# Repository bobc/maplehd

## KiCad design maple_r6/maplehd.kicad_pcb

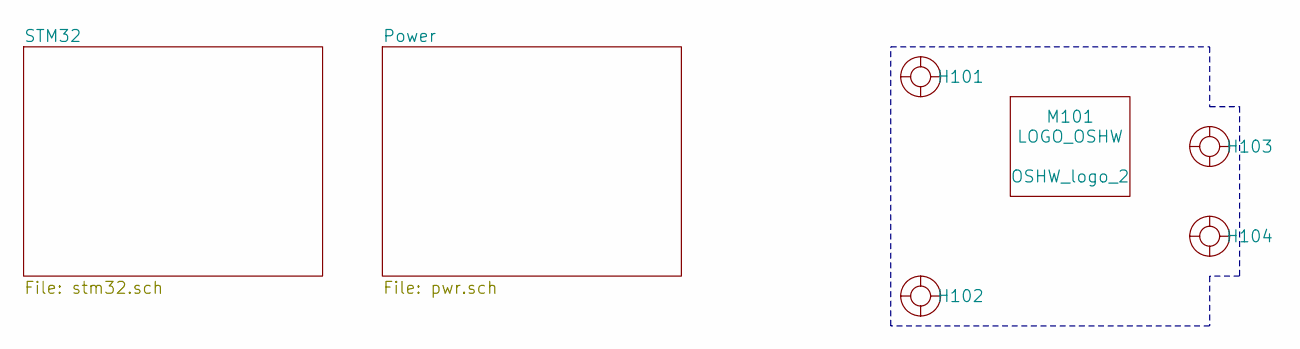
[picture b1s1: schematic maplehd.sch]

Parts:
H101, H102, H103, H104: HOLE_RMC
M101: LOGO_OSHW; OSHW_logo_2

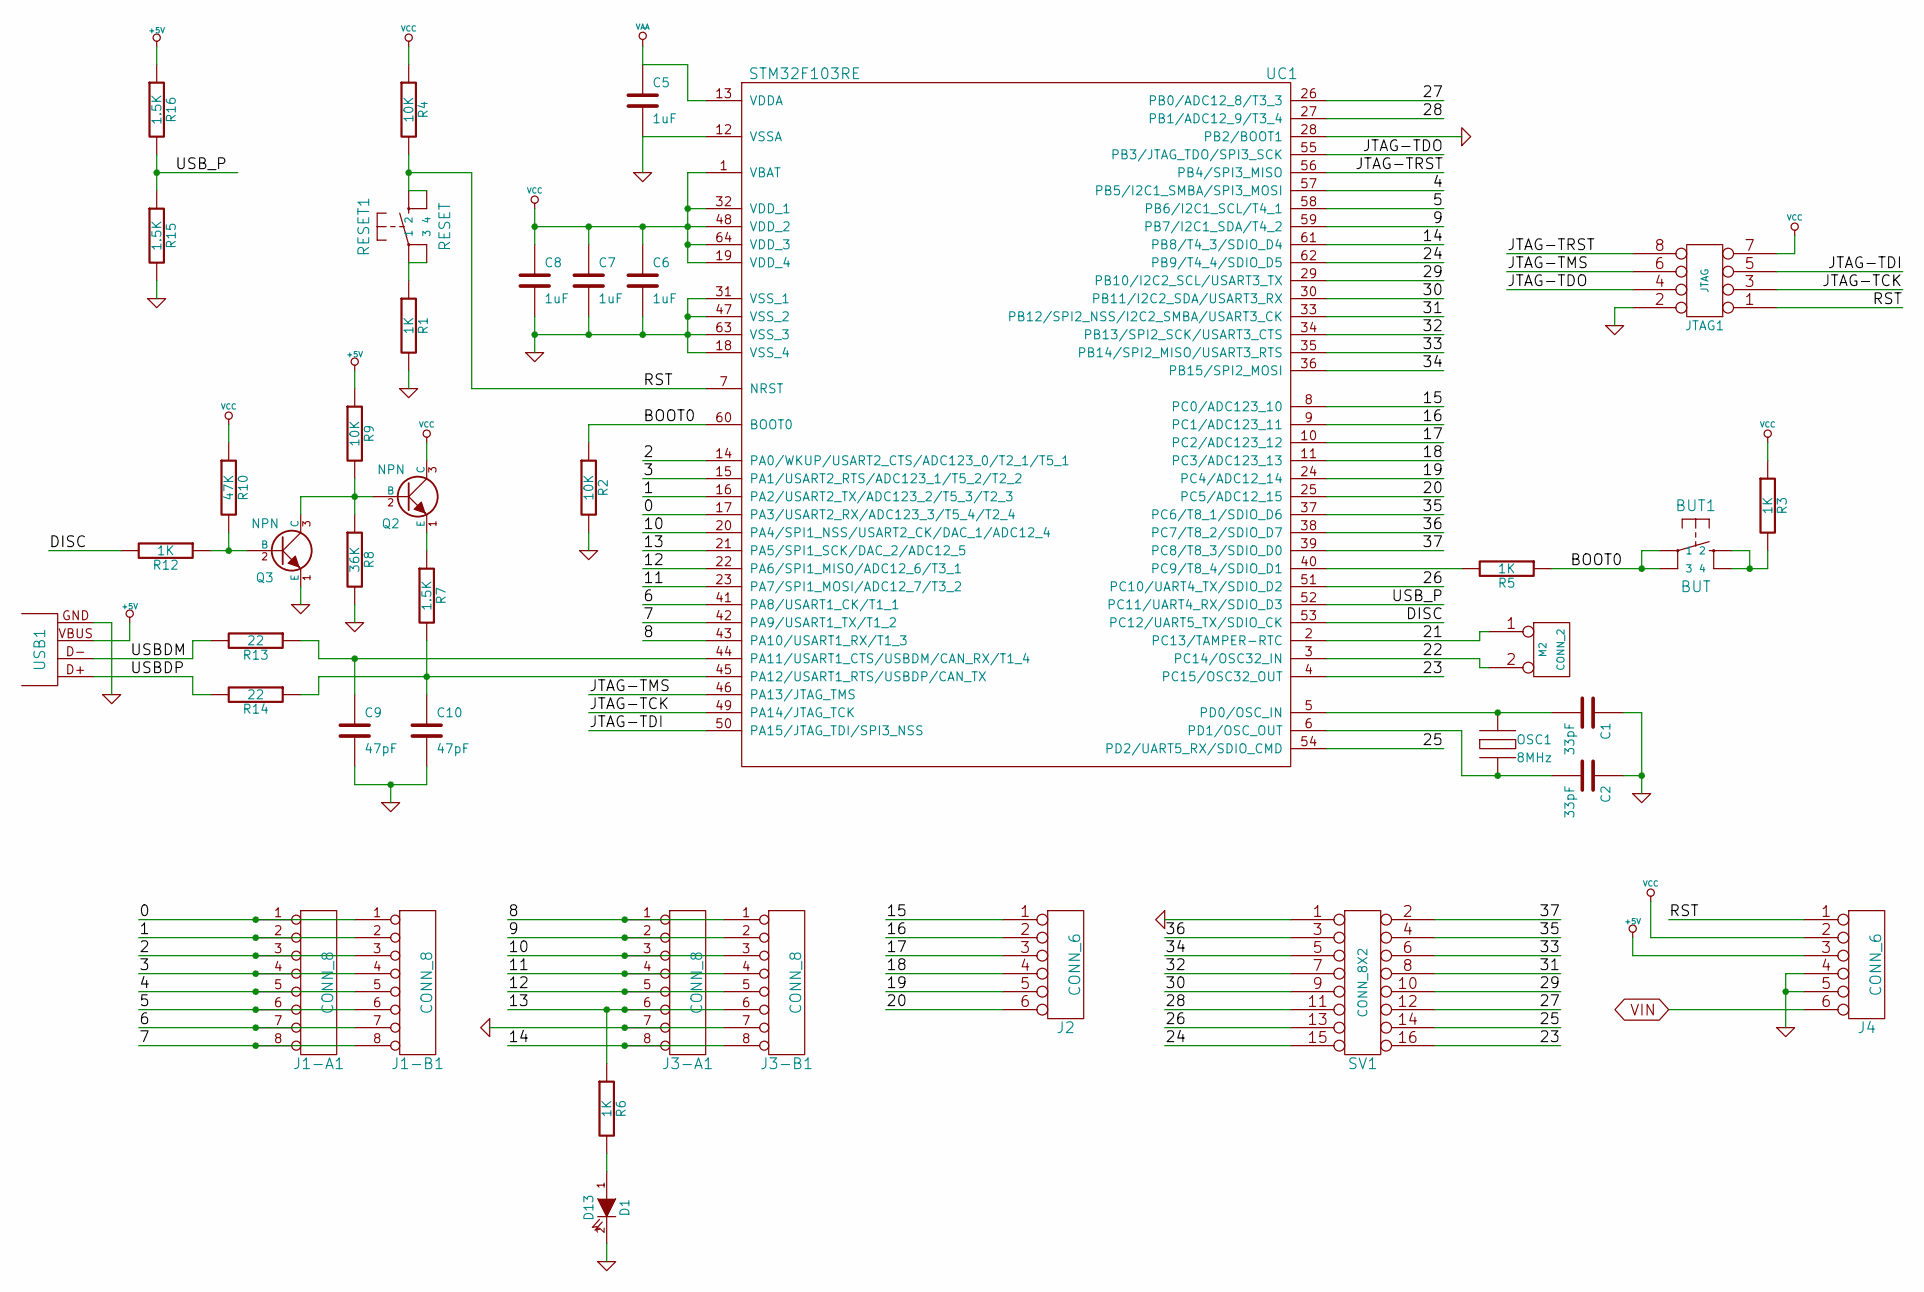
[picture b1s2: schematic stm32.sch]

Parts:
BUT1: BUT
C1, C2: 33pF
C5, C6, C7, C8: 1uF
C9, C10: 47pF
D1: D13
J1-A1, J1-B1, J3-A1, J3-B1: CONN_8
J2, J4: CONN_6
JTAG1: JTAG
M2: CONN_2
OSC1: 8MHz
Q2, Q3: NPN
R1, R3, R5, R6, R12: 1K
R2, R4, R9: 10K
R7, R15, R16: 1.5K
R8: 36K
R10: 47K
R13, R14: 22
RESET1: RESET
SV1: CONN_8X2
UC1: STM32F103RE
USB1: USB

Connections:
+5V: J4.3, R9.1, R16.1, USB1.VBUS; also elsewhere on the board
/STM32/0: J1-A1.1, J1-B1.1, UC1.17 (PA3/USART2_RX/ADC123_3/T5_4/T2_4)
/STM32/1: J1-A1.2, J1-B1.2, UC1.16 (PA2/USART2_TX/ADC123_2/T5_3/T2_3)
/STM32/2: J1-A1.3, J1-B1.3, UC1.14 (PA0/WKUP/USART2_CTS/ADC123_0/T2_1/T5_1)
/STM32/3: J1-A1.4, J1-B1.4, UC1.15 (PA1/USART2_RTS/ADC123_1/T5_2/T2_2)
/STM32/4: J1-A1.5, J1-B1.5, UC1.57 (PB5/I2C1_SMBA/SPI3_MOSI)
/STM32/5: J1-A1.6, J1-B1.6, UC1.58 (PB6/I2C1_SCL/T4_1)
/STM32/6: J1-A1.7, J1-B1.7, UC1.41 (PA8/USART1_CK/T1_1)
/STM32/7: J1-A1.8, J1-B1.8, UC1.42 (PA9/USART1_TX/T1_2)
/STM32/8: J3-A1.1, J3-B1.1, UC1.43 (PA10/USART1_RX/T1_3)
/STM32/9: J3-A1.2, J3-B1.2, UC1.59 (PB7/I2C1_SDA/T4_2)
/STM32/10: J3-A1.3, J3-B1.3, UC1.20 (PA4/SPI1_NSS/USART2_CK/DAC_1/ADC12_4)
/STM32/11: J3-A1.4, J3-B1.4, UC1.23 (PA7/SPI1_MOSI/ADC12_7/T3_2)
/STM32/12: J3-A1.5, J3-B1.5, UC1.22 (PA6/SPI1_MISO/ADC12_6/T3_1)
/STM32/13: J3-A1.6, J3-B1.6, R6.1, UC1.21 (PA5/SPI1_SCK/DAC_2/ADC12_5)
/STM32/14: J3-A1.8, J3-B1.8, UC1.61 (PB8/T4_3/SDIO_D4)
/STM32/15: J2.1, UC1.8 (PC0/ADC123_10)
/STM32/16: J2.2, UC1.9 (PC1/ADC123_11)
/STM32/17: J2.3, UC1.10 (PC2/ADC123_12)
/STM32/18: J2.4, UC1.11 (PC3/ADC123_13)
/STM32/19: J2.5, UC1.24 (PC4/ADC12_14)
/STM32/20: J2.6, UC1.25 (PC5/ADC12_15)
/STM32/21: M2.1, UC1.2 (PC13/TAMPER-RTC)
/STM32/22: M2.2 (PM), UC1.3 (PC14/OSC32_IN)
/STM32/23: SV1.16, UC1.4 (PC15/OSC32_OUT)
/STM32/24: SV1.15, UC1.62 (PB9/T4_4/SDIO_D5)
/STM32/25: SV1.14, UC1.54 (PD2/UART5_RX/SDIO_CMD)
/STM32/26: SV1.13, UC1.51 (PC10/UART4_TX/SDIO_D2)
/STM32/27: SV1.12, UC1.26 (PB0/ADC12_8/T3_3)
/STM32/28: SV1.11, UC1.27 (PB1/ADC12_9/T3_4)
/STM32/29: SV1.10, UC1.29 (PB10/I2C2_SCL/USART3_TX)
/STM32/30: SV1.9, UC1.30 (PB11/I2C2_SDA/USART3_RX)
/STM32/31: SV1.8, UC1.33 (PB12/SPI2_NSS/I2C2_SMBA/USART3_CK)
/STM32/32: SV1.7, UC1.34 (PB13/SPI2_SCK/USART3_CTS)
/STM32/33: SV1.6, UC1.35 (PB14/SPI2_MISO/USART3_RTS)
/STM32/34: SV1.5, UC1.36 (PB15/SPI2_MOSI)
/STM32/35: SV1.4, UC1.37 (PC6/T8_1/SDIO_D6)
/STM32/36: SV1.3, UC1.38 (PC7/T8_2/SDIO_D7)
/STM32/37: SV1.2, UC1.39 (PC8/T8_3/SDIO_D0)
/STM32/BOOT0: BUT1.1, BUT1.3, R2.1, R5.1, UC1.60 (BOOT0)
/STM32/DISC: R12.2, UC1.53 (PC12/UART5_TX/SDIO_CK)
/STM32/JTAG-TCK: JTAG1.3, UC1.49 (PA14/JTAG_TCK)
/STM32/JTAG-TDI: JTAG1.5, UC1.50 (PA15/JTAG_TDI/SPI3_NSS)
/STM32/JTAG-TDO: JTAG1.4, UC1.55 (PB3/JTAG_TDO/SPI3_SCK)
/STM32/JTAG-TMS: JTAG1.6, UC1.46 (PA13/JTAG_TMS)
/STM32/JTAG-TRST: JTAG1.8, UC1.56 (PB4/SPI3_MISO)
/STM32/RST: J4.1, JTAG1.1, R4.2, RESET1.2, RESET1.4, UC1.7 (NRST)
/STM32/USBDM: R13.2, USB1.D-
/STM32/USBDP: R14.2, USB1.D+
/STM32/USB_P: R15.1, R16.2, UC1.52 (PC11/UART4_RX/SDIO_D3)
GND: C1.1, C2.1, C5.2, C6.2, C7.2, C8.2, C9.2, C10.2, D1.2 (K), J3-A1.7, J3-B1.7, J4.4, J4.5, JTAG1.2, Q3.1 (E), R1.2, R2.2, R8.2, R15.2, SV1.1, UC1.12 (VSSA), UC1.18 (VSS_4), UC1.28 (PB2/BOOT1), UC1.31 (VSS_1), UC1.47 (VSS_2), UC1.63 (VSS_3), USB1.GND; also elsewhere on the board
unnamed: C2.2, OSC1.3, UC1.6 (PD1/OSC_OUT)
unnamed: C1.2, OSC1.1, UC1.5 (PD0/OSC_IN)
unnamed: R1.1, RESET1.1, RESET1.3
unnamed: Q2.1 (E), R7.1
unnamed: Q3.2 (B), R10.2, R12.1
unnamed: C10.1, R7.2, R14.1, UC1.45 (PA12/USART1_RTS/USBDP/CAN_TX)
unnamed: R5.2, UC1.40 (PC9/T8_4/SDIO_D1)
unnamed: D1.1 (A), R6.2
unnamed: C9.1, R13.1, UC1.44 (PA11/USART1_CTS/USBDM/CAN_RX/T1_4)
unnamed: Q2.2 (B), Q3.3 (C), R8.1, R9.2
unnamed: BUT1.2, BUT1.4, R3.2
VAA: C5.1, UC1.13 (VDDA); also elsewhere on the board
VCC: C6.1, C7.1, C8.1, J4.2, JTAG1.7, Q2.3 (C), R3.1, R4.1, R10.1, UC1.1 (VBAT), UC1.19 (VDD_4), UC1.32 (VDD_1), UC1.48 (VDD_2), UC1.64 (VDD_3); also elsewhere on the board
VIN: J4.6; also elsewhere on the board

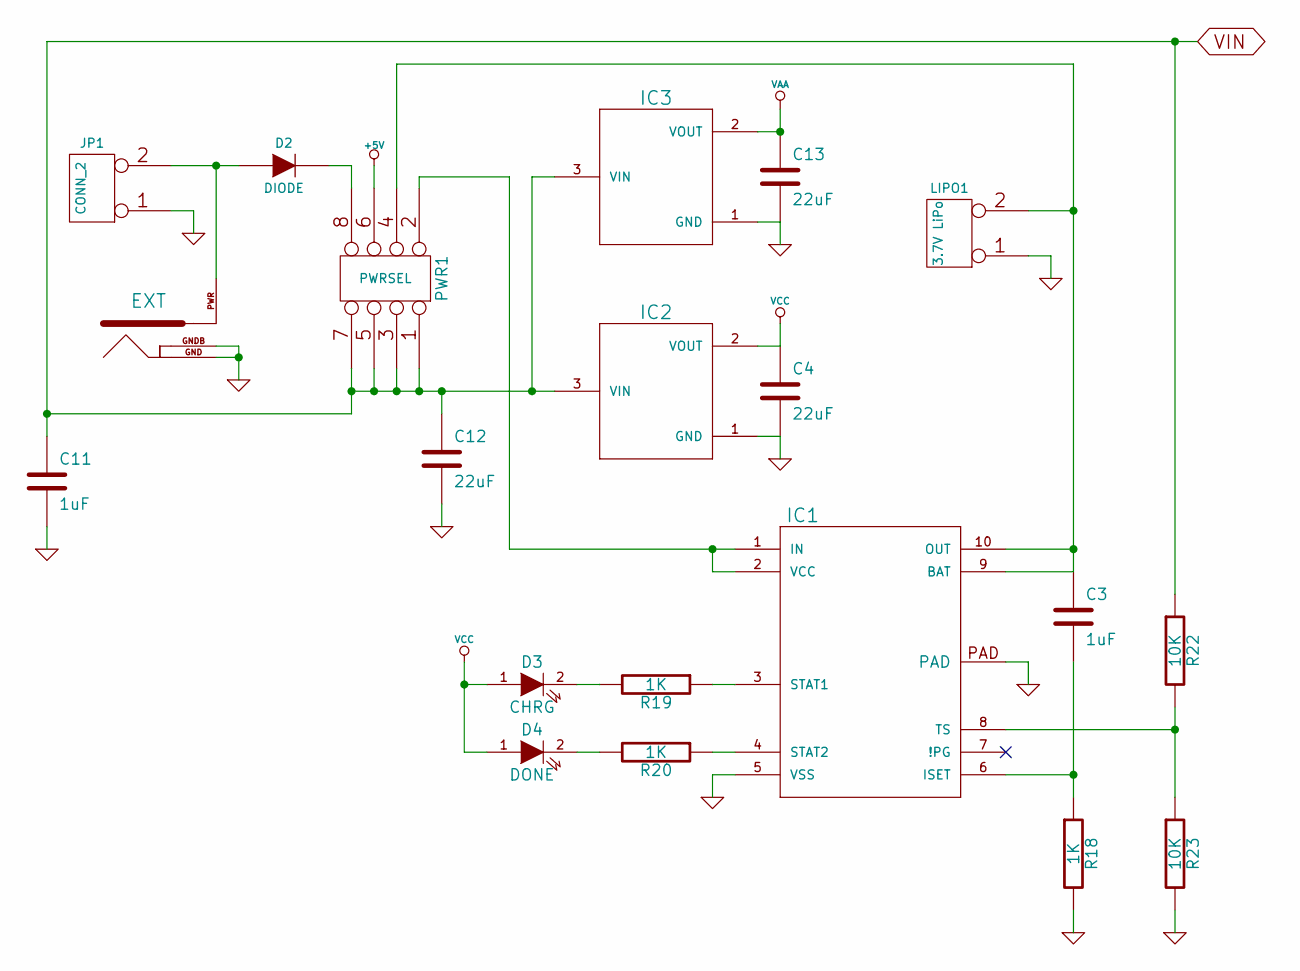
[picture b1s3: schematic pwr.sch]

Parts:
C3, C11: 1uF
C4, C12, C13: 22uF
D2: DIODE
D3: CHRG
D4: DONE
External1: EXT
IC1: BQ24010DRC
IC2, IC3: MCP1700T
JP1: CONN_2
LIPO1: 3.7V LiPo
PWR1: PWRSEL
R18, R19, R20: 1K
R22, R23: 10K

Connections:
+5V: PWR1.6; also elsewhere on the board
GND: C4.2, C11.2, C12.2, C13.2, External1.GND, External1.GNDB, IC1.5 (VSS), IC1.PAD, IC2.1 (GND), IC3.1 (GND), JP1.1, LIPO1.1, R18.2, R23.2; also elsewhere on the board
unnamed: IC1.8 (TS), R22.2, R23.1
unnamed: C3.2, IC1.6 (ISET), R18.1
unnamed: IC1.1 (IN), IC1.2 (VCC), PWR1.2
unnamed: D3.2 (K), R19.2
unnamed: IC1.4 (STAT2), R20.1
unnamed: D2.1 (A), External1.PWR, JP1.2 (PM)
unnamed: D2.2 (K), PWR1.8
unnamed: IC1.3 (STAT1), R19.1
unnamed: D4.2 (K), R20.2
unnamed: C3.1, IC1.9 (BAT), IC1.10 (OUT), LIPO1.2 (PM), PWR1.4
VAA: C13.1, IC3.2 (VOUT); also elsewhere on the board
VCC: C4.1, D3.1 (A), D4.1 (A), IC2.2 (VOUT); also elsewhere on the board
VIN: C11.1, C12.1, IC2.3 (VIN), IC3.3 (VIN), PWR1.1, PWR1.3, PWR1.5, PWR1.7, R22.1; also elsewhere on the board

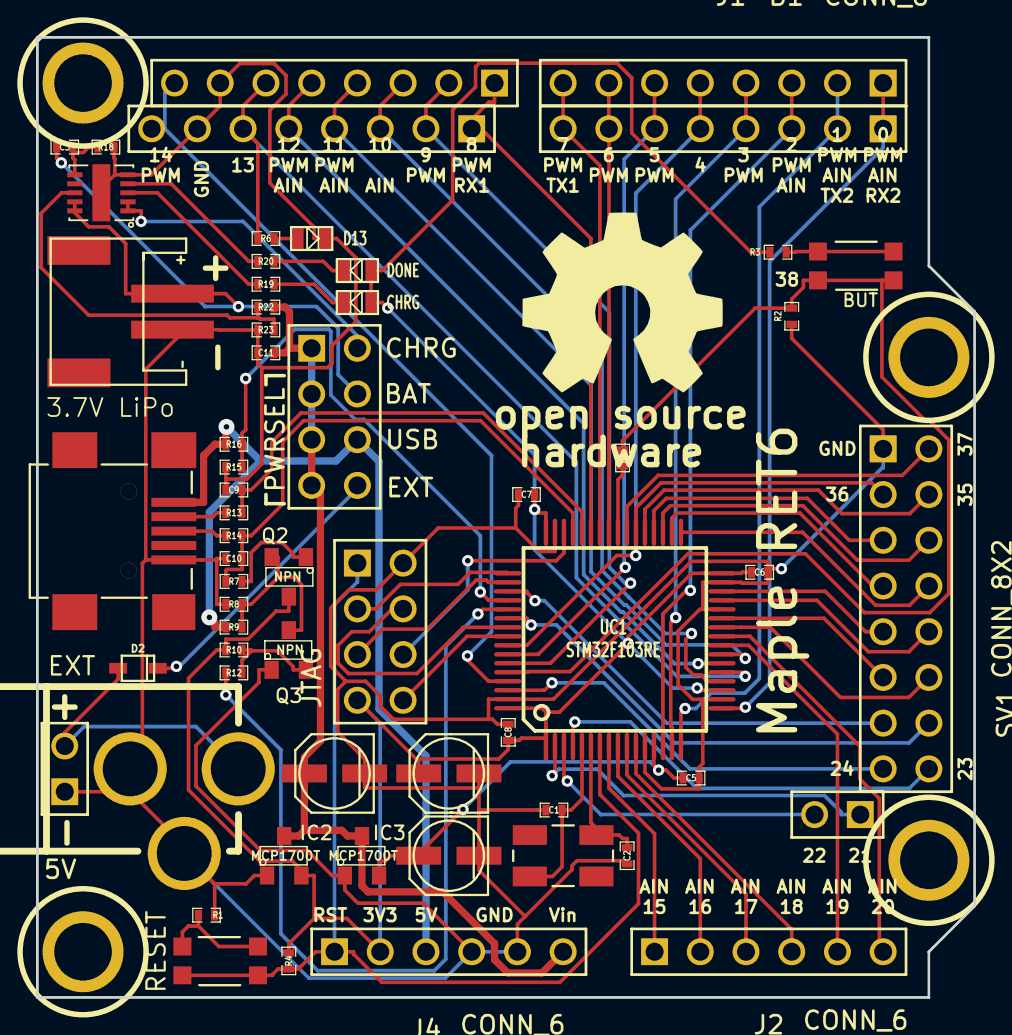
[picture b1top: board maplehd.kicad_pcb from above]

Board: 2 copper layers, 52.1 x 53.3 mm, 66 parts (0 on the bottom side), 75 nets.

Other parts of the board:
pcb_maple: VAL**; pcb_maple

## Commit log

2015-05-11 Move project files to subfolder.
2015-05-11 Add common kicad libraries
2015-05-11 Add project specific libraries to hardware-lib
2015-05-11 R6v1 : Updated schematic and created PCB layout
